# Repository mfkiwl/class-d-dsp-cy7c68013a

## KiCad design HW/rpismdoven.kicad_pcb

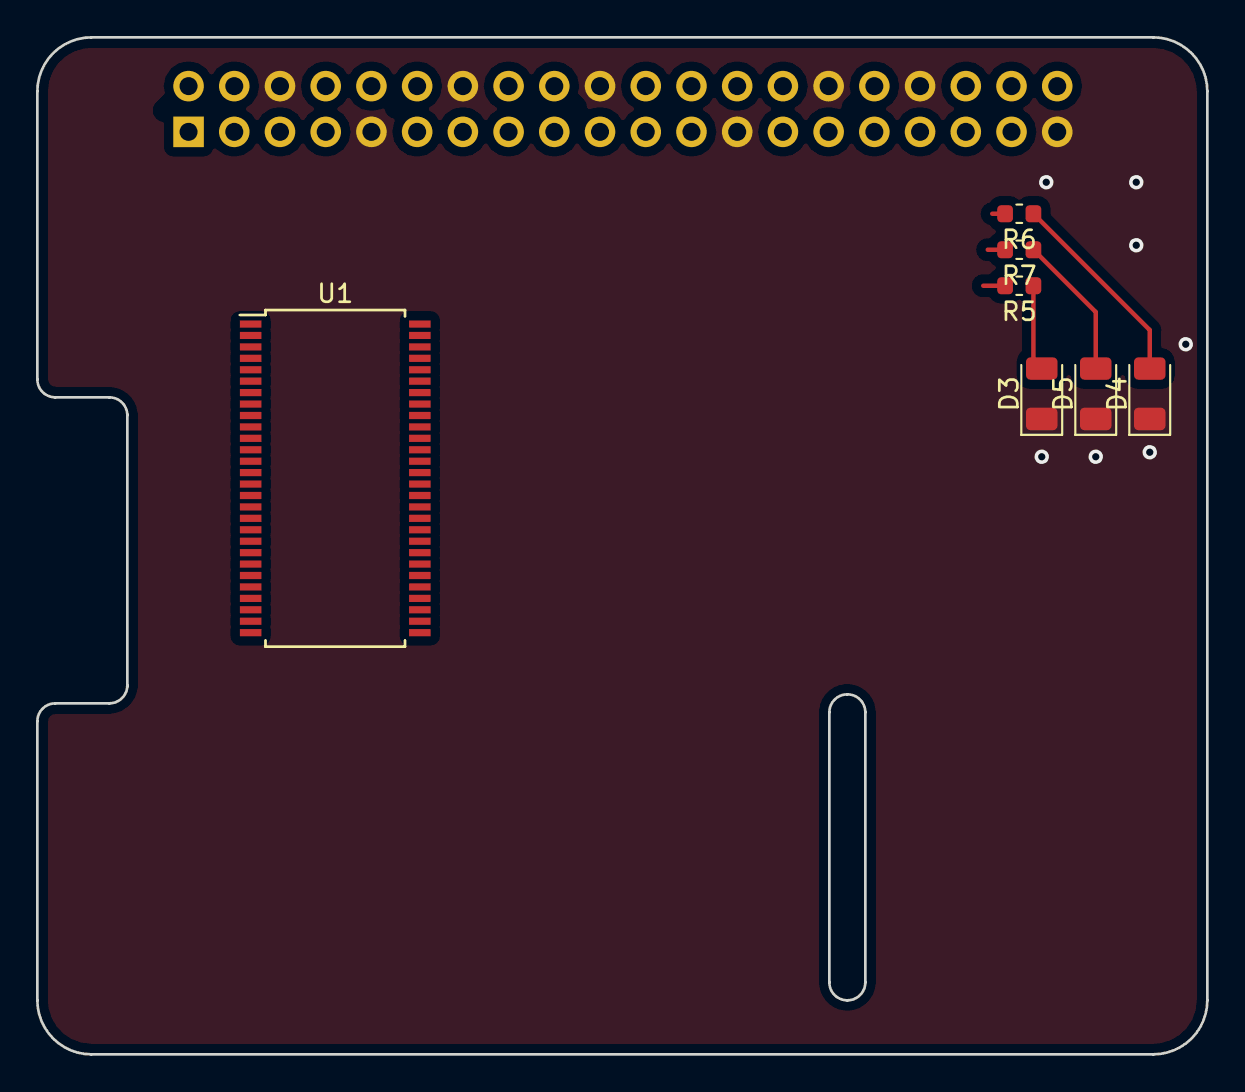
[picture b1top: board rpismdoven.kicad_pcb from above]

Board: 2 copper layers, 65.0 x 56.5 mm, 8 parts (1 on the bottom side), 13 nets.

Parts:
D3, D4, D5: LED; D_1206_3216Metric
J1: Raspberry_Pi_2_3; PinSocket_2x20_P2.54mm_Vertical
R5, R6, R7: R_Small; R_0603_1608Metric
U1: CY7C68013A-56PVX; SSOP-56_7.5x18.5mm_P0.635mm

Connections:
+3V3: J1.1, J1.17
+5V: J1.2, J1.4
GND: D3.1, D4.1, D5.1, J1.6, J1.9, J1.14, J1.20, J1.25, J1.30, J1.34, J1.39
unnamed: D3.2, R5.1
unnamed: D4.2, R6.1
unnamed: D5.2, R7.1
unnamed: J1.27, R5.2
unnamed: J1.29, R6.2
unnamed: J1.31, R7.2
unnamed: U1.10, U1.14
unnamed: U1.13, U1.17
unnamed: U1.6, U1.18, U1.24, U1.34, U1.39, U1.50
unnamed: U1.4, U1.7, U1.19, U1.33, U1.35, U1.48

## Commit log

2019-03-13 initial HW
